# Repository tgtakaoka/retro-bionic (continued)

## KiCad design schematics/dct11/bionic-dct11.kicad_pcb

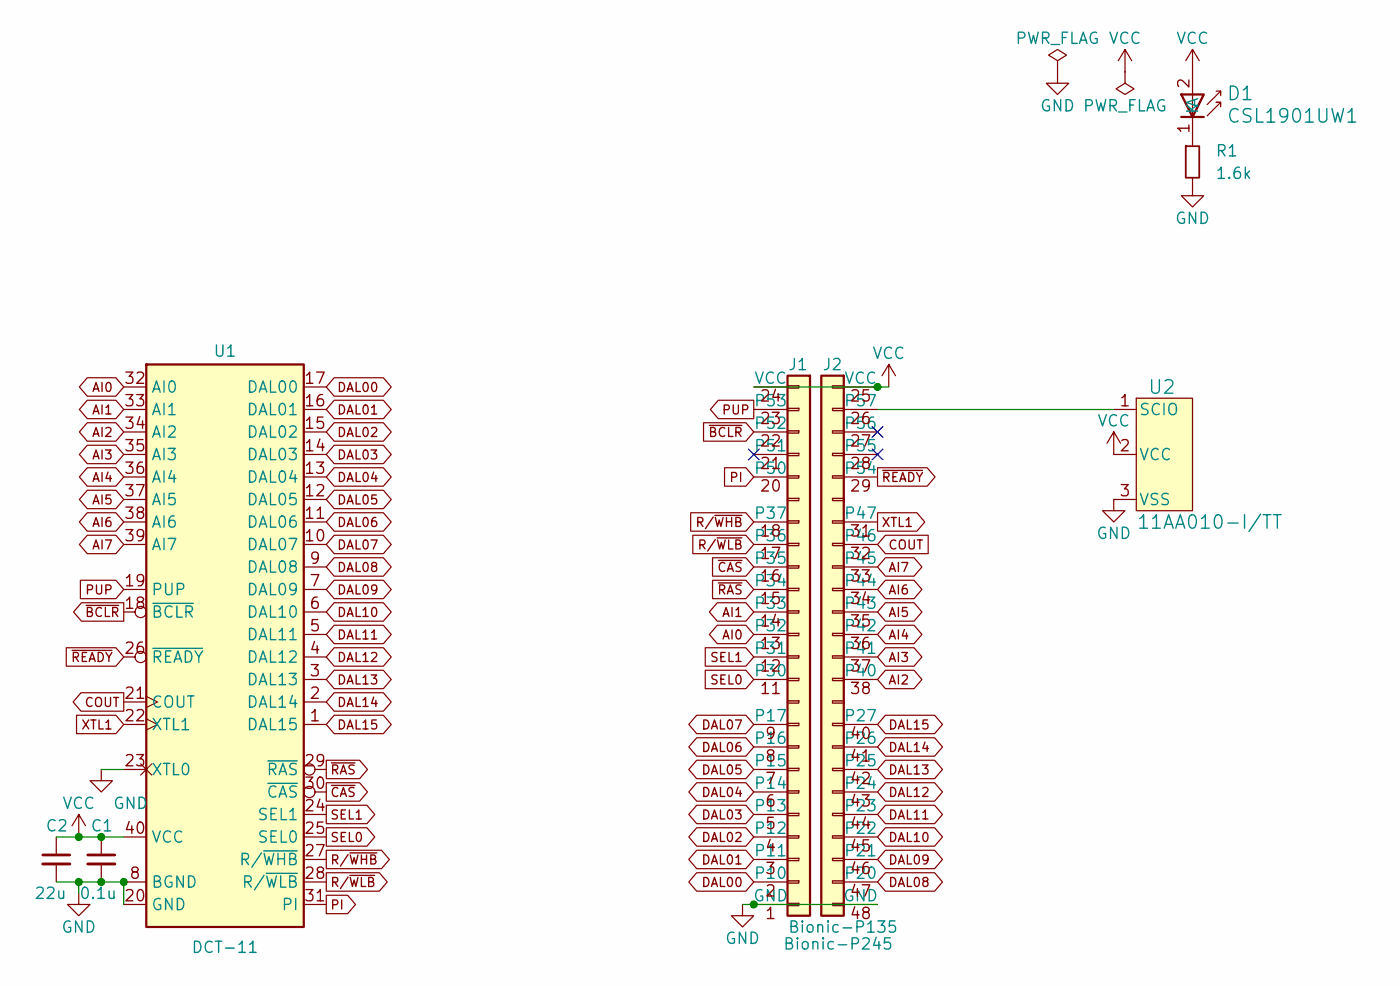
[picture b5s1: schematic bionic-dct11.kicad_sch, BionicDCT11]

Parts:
C1: 0.1u; C_0603_1608Metric_Pad1.08x0.95mm_HandSolder
C2: 22u; C_0603_1608Metric_Pad1.08x0.95mm_HandSolder
D1: CSL1901UW1; LED_CSL1901UW1_ROM-M
J1: Bionic-P135; Bionic-P135_THT
J2: Bionic-P245; Bionic-P245_THT
R1: 1.6k; R_0603_1608Metric_Pad0.98x0.95mm_HandSolder
U1: DCT-11; DIP-40_W15.24mm_Socket
U2: 11AA010-I/TT; SOT-23_MC_MCH-M

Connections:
AI0: J1.13 (P32), U1.32 (AI0)
AI1: J1.14 (P33), U1.33 (AI1)
AI2: J2.38 (P40), U1.34 (AI2)
AI3: J2.37 (P41), U1.35 (AI3)
AI4: J2.36 (P42), U1.36 (AI4)
AI5: J2.35 (P43), U1.37 (AI5)
AI6: J2.34 (P44), U1.38 (AI6)
AI7: J2.33 (P45), U1.39 (AI7)
COUT: J2.32 (P46), U1.21 (COUT)
DAL00: J1.2 (P10), U1.17 (DAL00)
DAL01: J1.3 (P11), U1.16 (DAL01)
DAL02: J1.4 (P12), U1.15 (DAL02)
DAL03: J1.5 (P13), U1.14 (DAL03)
DAL04: J1.6 (P14), U1.13 (DAL04)
DAL05: J1.7 (P15), U1.12 (DAL05)
DAL06: J1.8 (P16), U1.11 (DAL06)
DAL07: J1.9 (P17), U1.10 (DAL07)
DAL08: J2.47 (P20), U1.9 (DAL08)
DAL09: J2.46 (P21), U1.7 (DAL09)
DAL10: J2.45 (P22), U1.6 (DAL10)
DAL11: J2.44 (P23), U1.5 (DAL11)
DAL12: J2.43 (P24), U1.4 (DAL12)
DAL13: J2.42 (P25), U1.3 (DAL13)
DAL14: J2.41 (P26), U1.2 (DAL14)
DAL15: J2.40 (P27), U1.1 (DAL15)
GND: C1.2, C2.2, J1.1 (GND), J2.48 (GND), R1.2, U1.8 (BGND), U1.20 (GND), U1.23 (XTL0), U2.3 (VSS)
unnamed: D1.1 (K), R1.1
unnamed: J2.26 (P57), U2.1 (SCIO)
PI: J1.20 (P50), U1.31 (PI)
PUP: J1.23 (P53), U1.19 (PUP)
R/~WHB: J1.18 (P37), U1.27 (R/~WHB)
R/~WLB: J1.17 (P36), U1.28 (R/~WLB)
SEL0: J1.11 (P30), U1.25 (SEL0)
SEL1: J1.12 (P31), U1.24 (SEL1)
VCC: C1.1, C2.1, D1.2 (A), J1.24 (VCC), J2.25 (VCC), U1.40 (VCC), U2.2 (VCC)
XTL1: J2.31 (P47), U1.22 (XTL1)
~BCLR: J1.22 (P52), U1.18 (~BCLR)
~CAS: J1.16 (P35), U1.30 (~CAS)
~RAS: J1.15 (P34), U1.29 (~RAS)
~READY: J2.29 (P54), U1.26 (~READY)

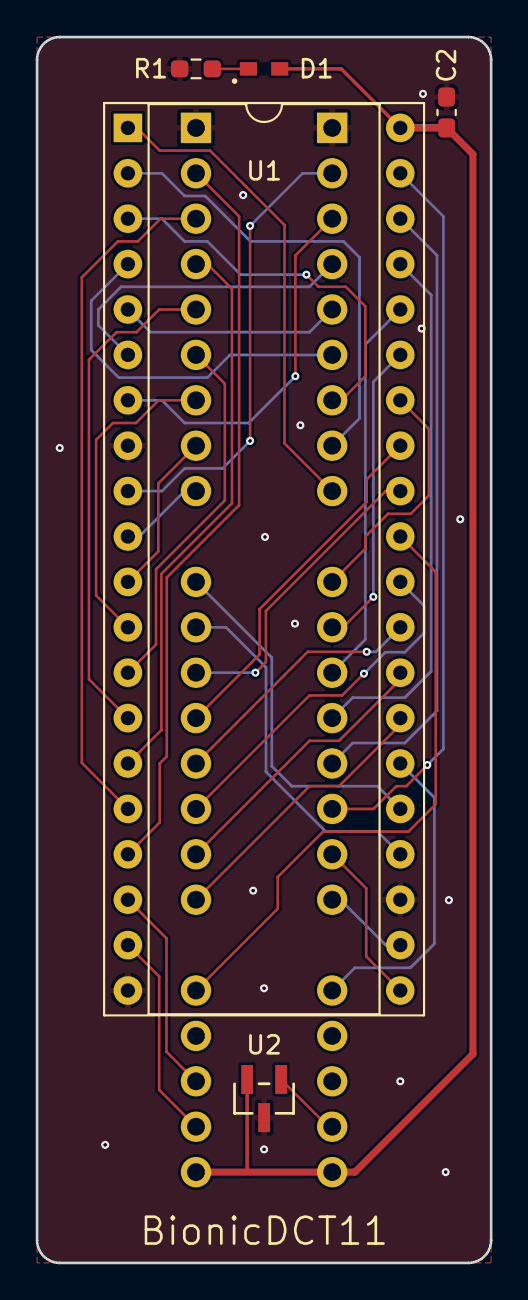
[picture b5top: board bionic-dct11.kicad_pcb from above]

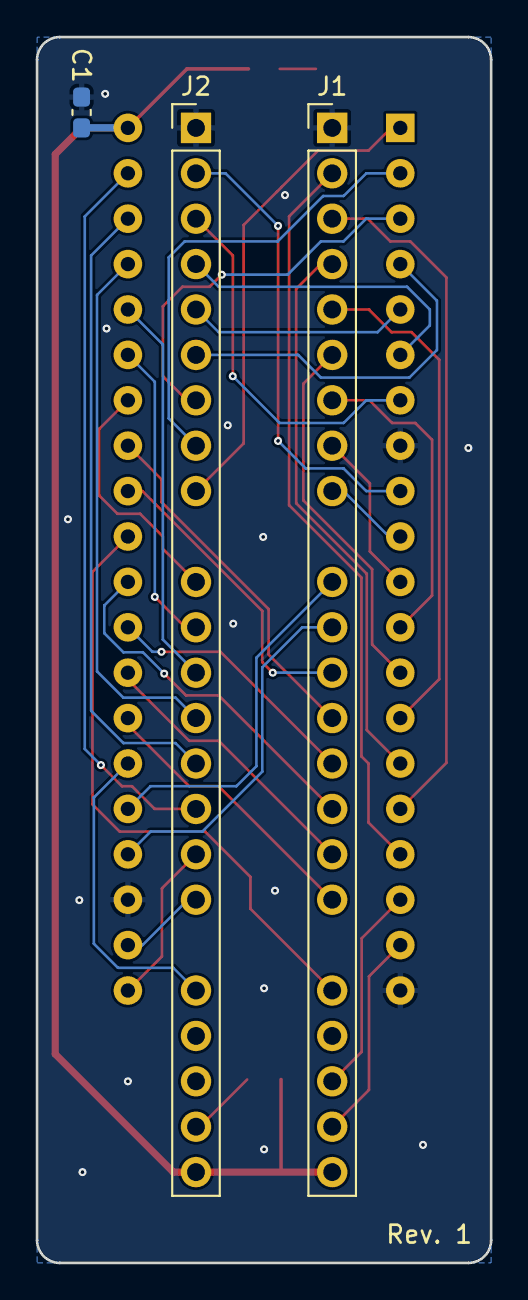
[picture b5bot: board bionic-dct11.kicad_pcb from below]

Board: 2 copper layers, 25.4 x 68.6 mm, 8 parts (3 on the bottom side), 40 nets.

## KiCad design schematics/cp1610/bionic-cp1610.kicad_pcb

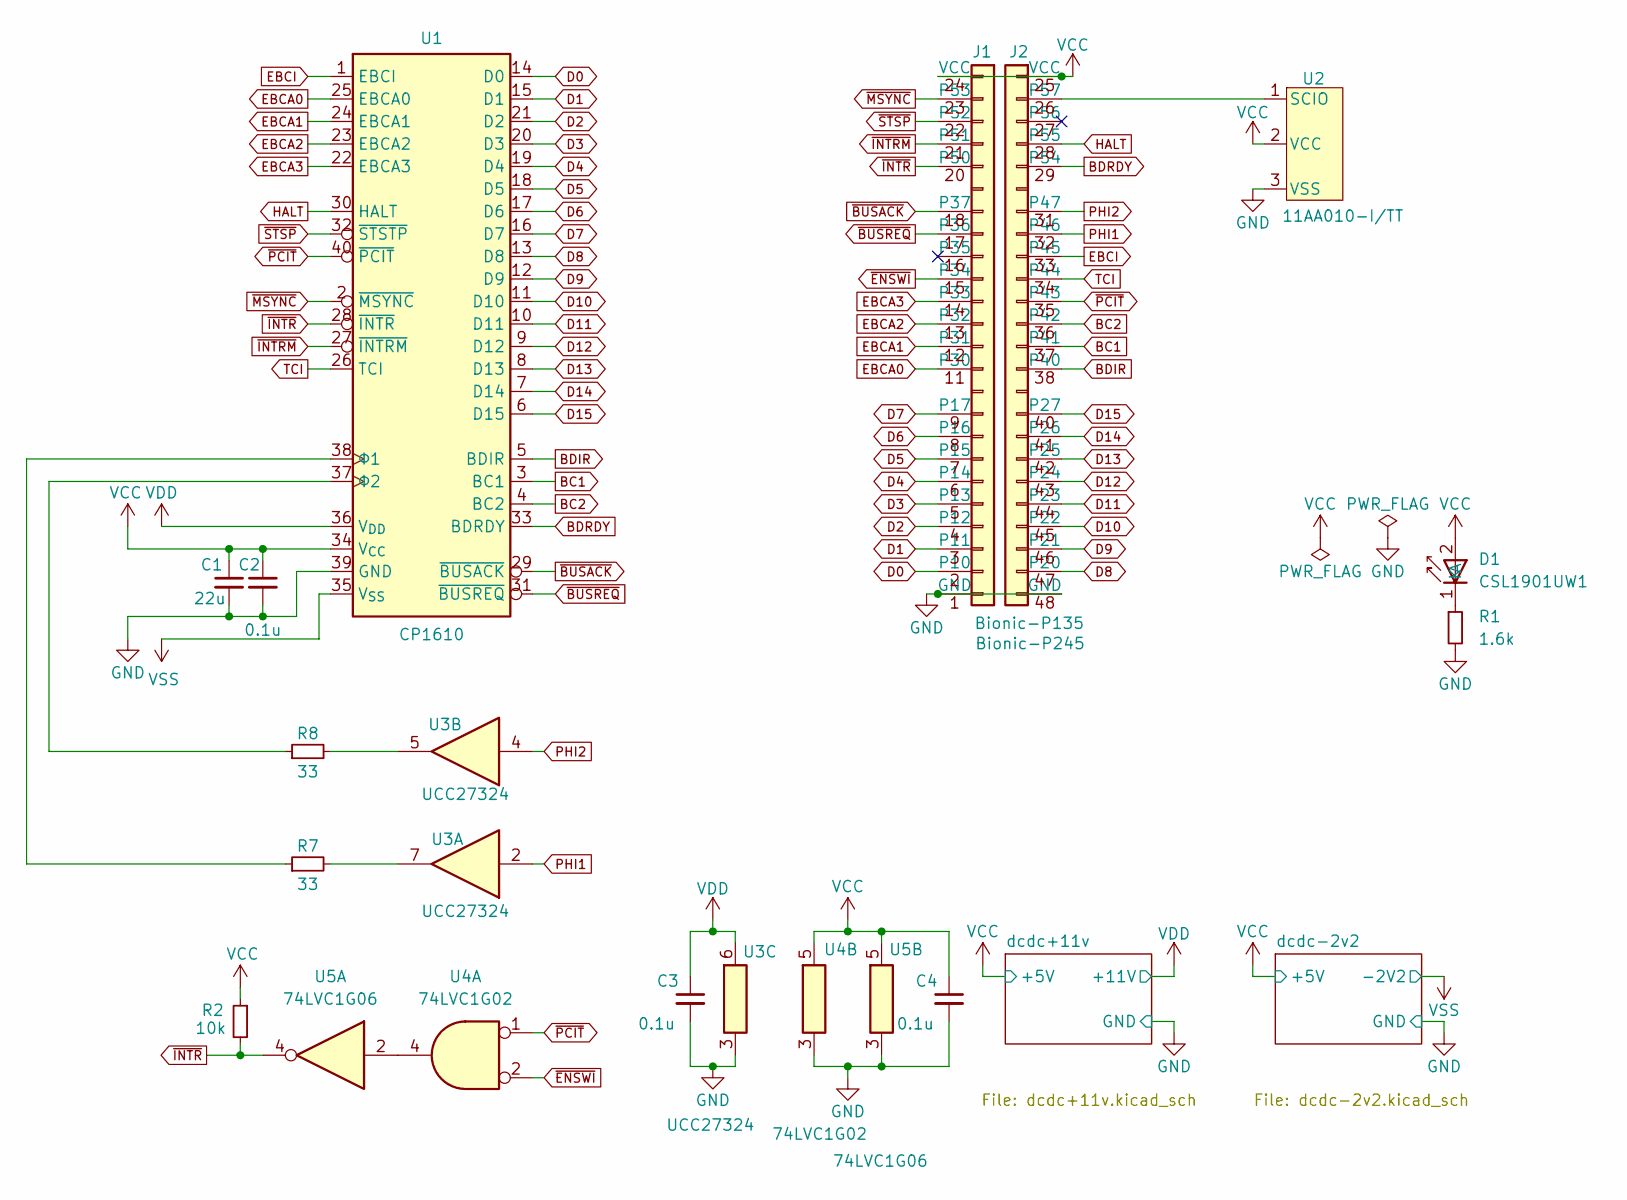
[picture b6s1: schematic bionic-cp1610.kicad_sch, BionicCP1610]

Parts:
C1: 22u; C_0603_1608Metric_Pad1.08x0.95mm_HandSolder
C2, C3, C4: 0.1u; C_0603_1608Metric_Pad1.08x0.95mm_HandSolder
D1: CSL1901UW1; LED_CSL1901UW1_ROM-M
J1: Bionic-P135; Bionic-P135_SMT
J2: Bionic-P245; Bionic-P245_SMT
R1: 1.6k; R_0603_1608Metric_Pad0.98x0.95mm_HandSolder
R2: 10k; R_0603_1608Metric_Pad0.98x0.95mm_HandSolder
R7, R8: 33; R_0603_1608Metric
U1: CP1610; DIP-40_W15.24mm_Socket
U2: 11AA010-I/TT; SOT-23_MC_MCH-M
U3: UCC27324; DGN8-M
U4: 74LVC1G02; DBV5-M
U5: 74LVC1G06; DBV5-M

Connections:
BC1: J2.37 (P41), U1.3 (BC1)
BC2: J2.36 (P42), U1.4 (BC2)
BDIR: J2.38 (P40), U1.5 (BDIR)
BDRDY: J2.29 (P54), U1.33 (BDRDY)
D0: J1.2 (P10), U1.14 (D0)
D1: J1.3 (P11), U1.15 (D1)
D2: J1.4 (P12), U1.21 (D2)
D3: J1.5 (P13), U1.20 (D3)
D4: J1.6 (P14), U1.19 (D4)
D5: J1.7 (P15), U1.18 (D5)
D6: J1.8 (P16), U1.17 (D6)
D7: J1.9 (P17), U1.16 (D7)
D8: J2.47 (P20), U1.13 (D8)
D9: J2.46 (P21), U1.12 (D9)
D10: J2.45 (P22), U1.11 (D10)
D11: J2.44 (P23), U1.10 (D11)
D12: J2.43 (P24), U1.9 (D12)
D13: J2.42 (P25), U1.8 (D13)
D14: J2.41 (P26), U1.7 (D14)
D15: J2.40 (P27), U1.6 (D15)
EBCA0: J1.11 (P30), U1.25 (EBCA0)
EBCA1: J1.12 (P31), U1.24 (EBCA1)
EBCA2: J1.13 (P32), U1.23 (EBCA2)
EBCA3: J1.14 (P33), U1.22 (EBCA3)
EBCI: J2.33 (P45), U1.1 (EBCI)
GND: C1.2, C2.2, C3.2, C4.2, J1.1 (GND), J2.48 (GND), R1.2, U1.39 (GND), U2.3 (VSS), U3.3 (GND), U4.3 (GND), U5.3 (GND); also elsewhere on the board
HALT: J2.28 (P55), U1.30 (HALT)
unnamed: D1.1 (K), R1.1
unnamed: J2.26 (P57), U2.1 (SCIO)
unnamed: R7.1, U1.38 (Φ1)
unnamed: R8.1, U1.37 (Φ2)
unnamed: R7.2, U3.7 (OUTA)
unnamed: R8.2, U3.5 (OUTB)
unnamed: U4.4, U5.2
PHI1: J2.32 (P46), U3.2 (INA)
PHI2: J2.31 (P47), U3.4 (INB)
TCI: J2.34 (P44), U1.26 (TCI)
VCC: C1.1, C2.1, C4.1, D1.2 (A), J1.24 (VCC), J2.25 (VCC), R2.1, U1.34 (V_{CC}), U2.2 (VCC), U4.5 (VCC), U5.5 (VCC); also elsewhere on the board
VDD: C3.1, U1.36 (V_{DD}), U3.6 (VDD); also elsewhere on the board
VSS: U1.35 (V_{SS}); also elsewhere on the board
~BUSACK: J1.18 (P37), U1.29 (~BUSACK)
~BUSREQ: J1.17 (P36), U1.31 (~BUSREQ)
~ENSWI: J1.15 (P34), U4.2
~INTRM: J1.21 (P51), U1.27 (~INTRM)
~INTR: J1.20 (P50), R2.2, U1.28 (~INTR), U5.4
~MSYNC: J1.23 (P53), U1.2 (~MSYNC)
~PCIT: J2.35 (P43), U1.40 (~PCIT), U4.1
~STSP: J1.22 (P52), U1.32 (~STSTP)

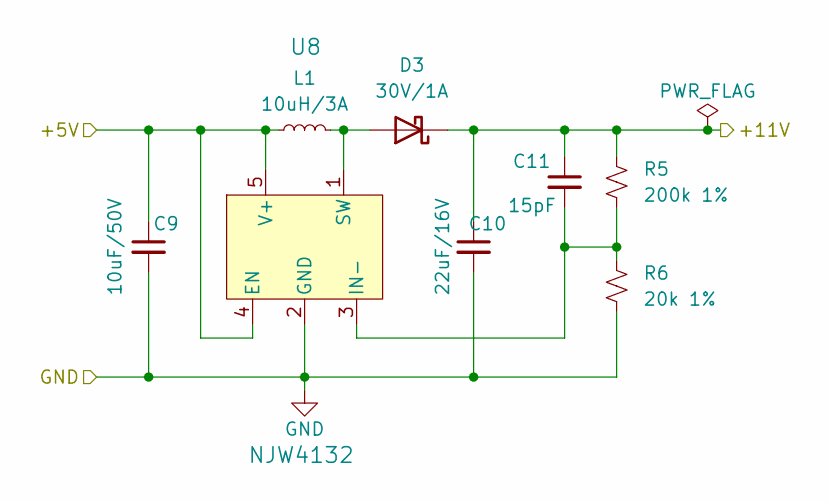
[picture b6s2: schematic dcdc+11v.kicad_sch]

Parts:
C9: 10uF/50V; C_0603_1608Metric_Pad1.08x0.95mm_HandSolder
C10: 22uF/16V; C_0603_1608Metric_Pad1.08x0.95mm_HandSolder
C11: 15pF; C_0603_1608Metric_Pad1.08x0.95mm_HandSolder
D3: 30V/1A; CR_60M-60_ROM-M
L1: 10uH/3A; IND_DFE322512F_MUR-M
R5: 200k 1%; R_0603_1608Metric_Pad0.98x0.95mm_HandSolder
R6: 20k 1%; R_0603_1608Metric_Pad0.98x0.95mm_HandSolder
U8: NJW4132; SOT-89-5_NMD-M

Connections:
GND: C9.2, C10.2, R6.2, U8.2 (GND); also elsewhere on the board
unnamed: D3.2 (A), L1.2, U8.1 (SW)
unnamed: C11.2, R5.2, R6.1, U8.3 (IN-)
VCC: C9.1, L1.1, U8.4 (EN), U8.5 (V+); also elsewhere on the board
VDD: C10.1, C11.1, D3.1 (K), R5.1; also elsewhere on the board

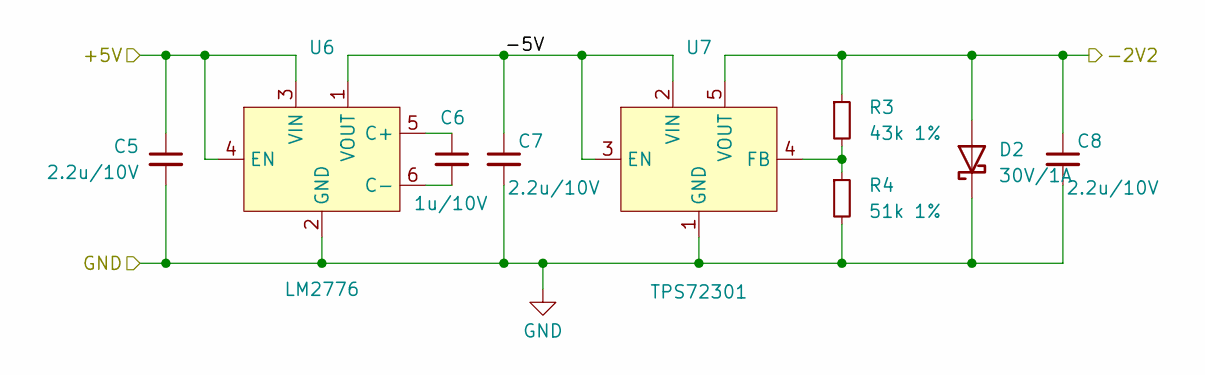
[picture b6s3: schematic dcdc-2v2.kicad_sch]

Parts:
C5, C7, C8: 2.2u/10V; C_0603_1608Metric_Pad1.08x0.95mm_HandSolder
C6: 1u/10V; C_0603_1608Metric_Pad1.08x0.95mm_HandSolder
D2: 30V/1A; CR_60M-60_ROM-M
R3: 43k 1%; R_0603_1608Metric_Pad0.98x0.95mm_HandSolder
R4: 51k 1%; R_0603_1608Metric_Pad0.98x0.95mm_HandSolder
U6: LM2776; DBV0006A_M
U7: TPS72301; DBV5-M

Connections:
/dcdc-2v2/-5V: C7.1, U6.1 (VOUT), U7.2 (VIN), U7.3 (EN)
GND: C5.2, C7.2, C8.2, D2.1 (K), R4.2, U6.2 (GND), U7.1 (GND); also elsewhere on the board
unnamed: C6.1, U6.5 (C+)
unnamed: C6.2, U6.6 (C-)
unnamed: R3.2, R4.1, U7.4 (FB)
VCC: C5.1, U6.3 (VIN), U6.4 (EN); also elsewhere on the board
VSS: C8.1, D2.2 (A), R3.1, U7.5 (VOUT); also elsewhere on the board

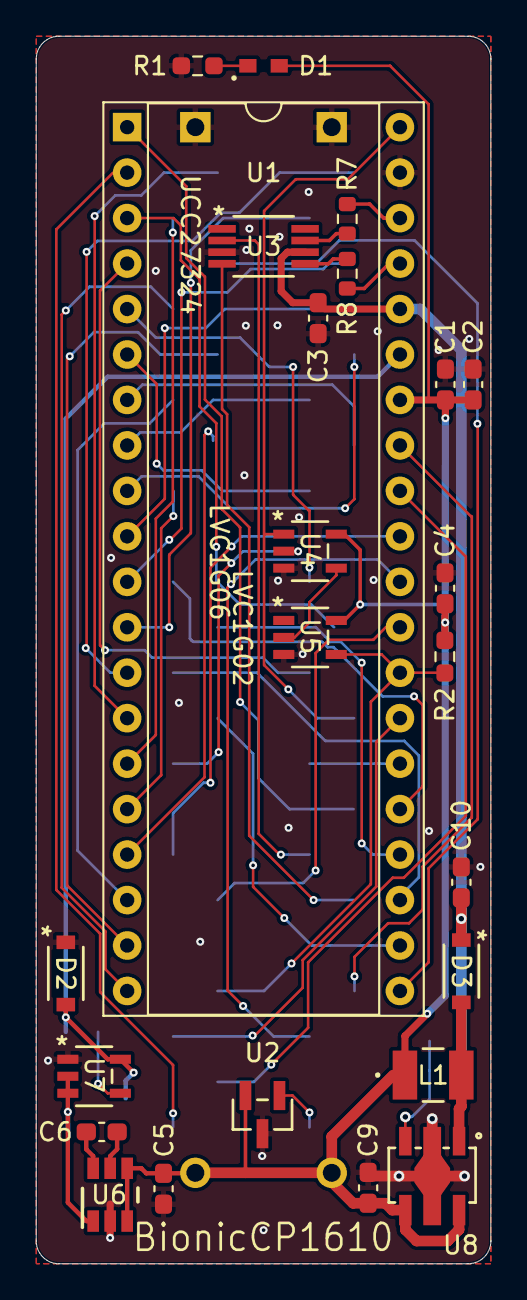
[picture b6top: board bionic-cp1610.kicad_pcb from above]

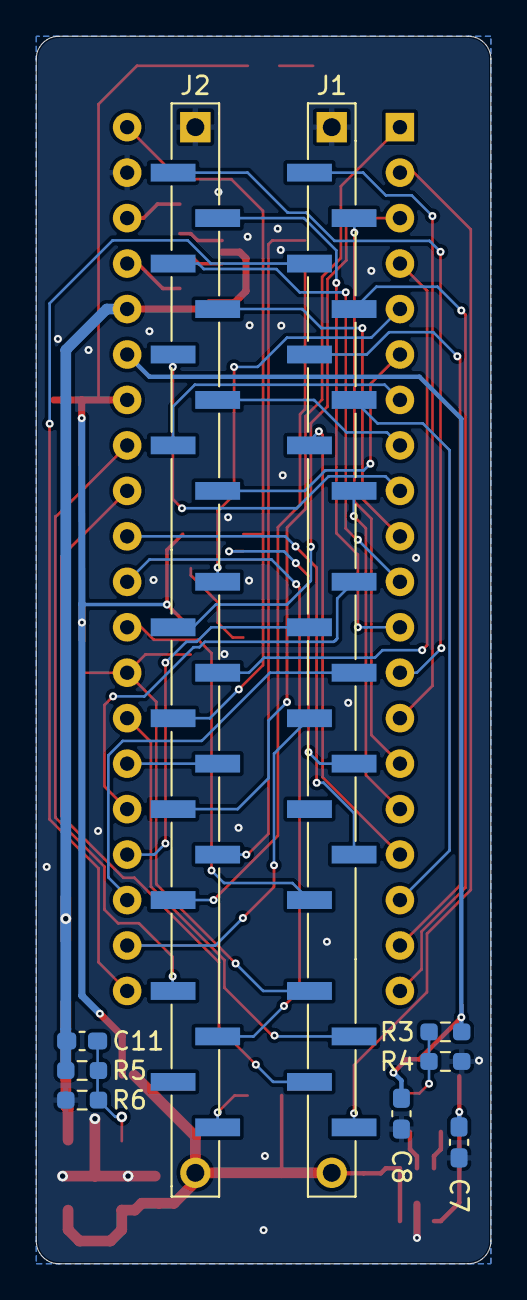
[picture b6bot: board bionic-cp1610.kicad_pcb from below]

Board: 2 copper layers, 25.4 x 68.6 mm, 33 parts (9 on the bottom side), 54 nets.

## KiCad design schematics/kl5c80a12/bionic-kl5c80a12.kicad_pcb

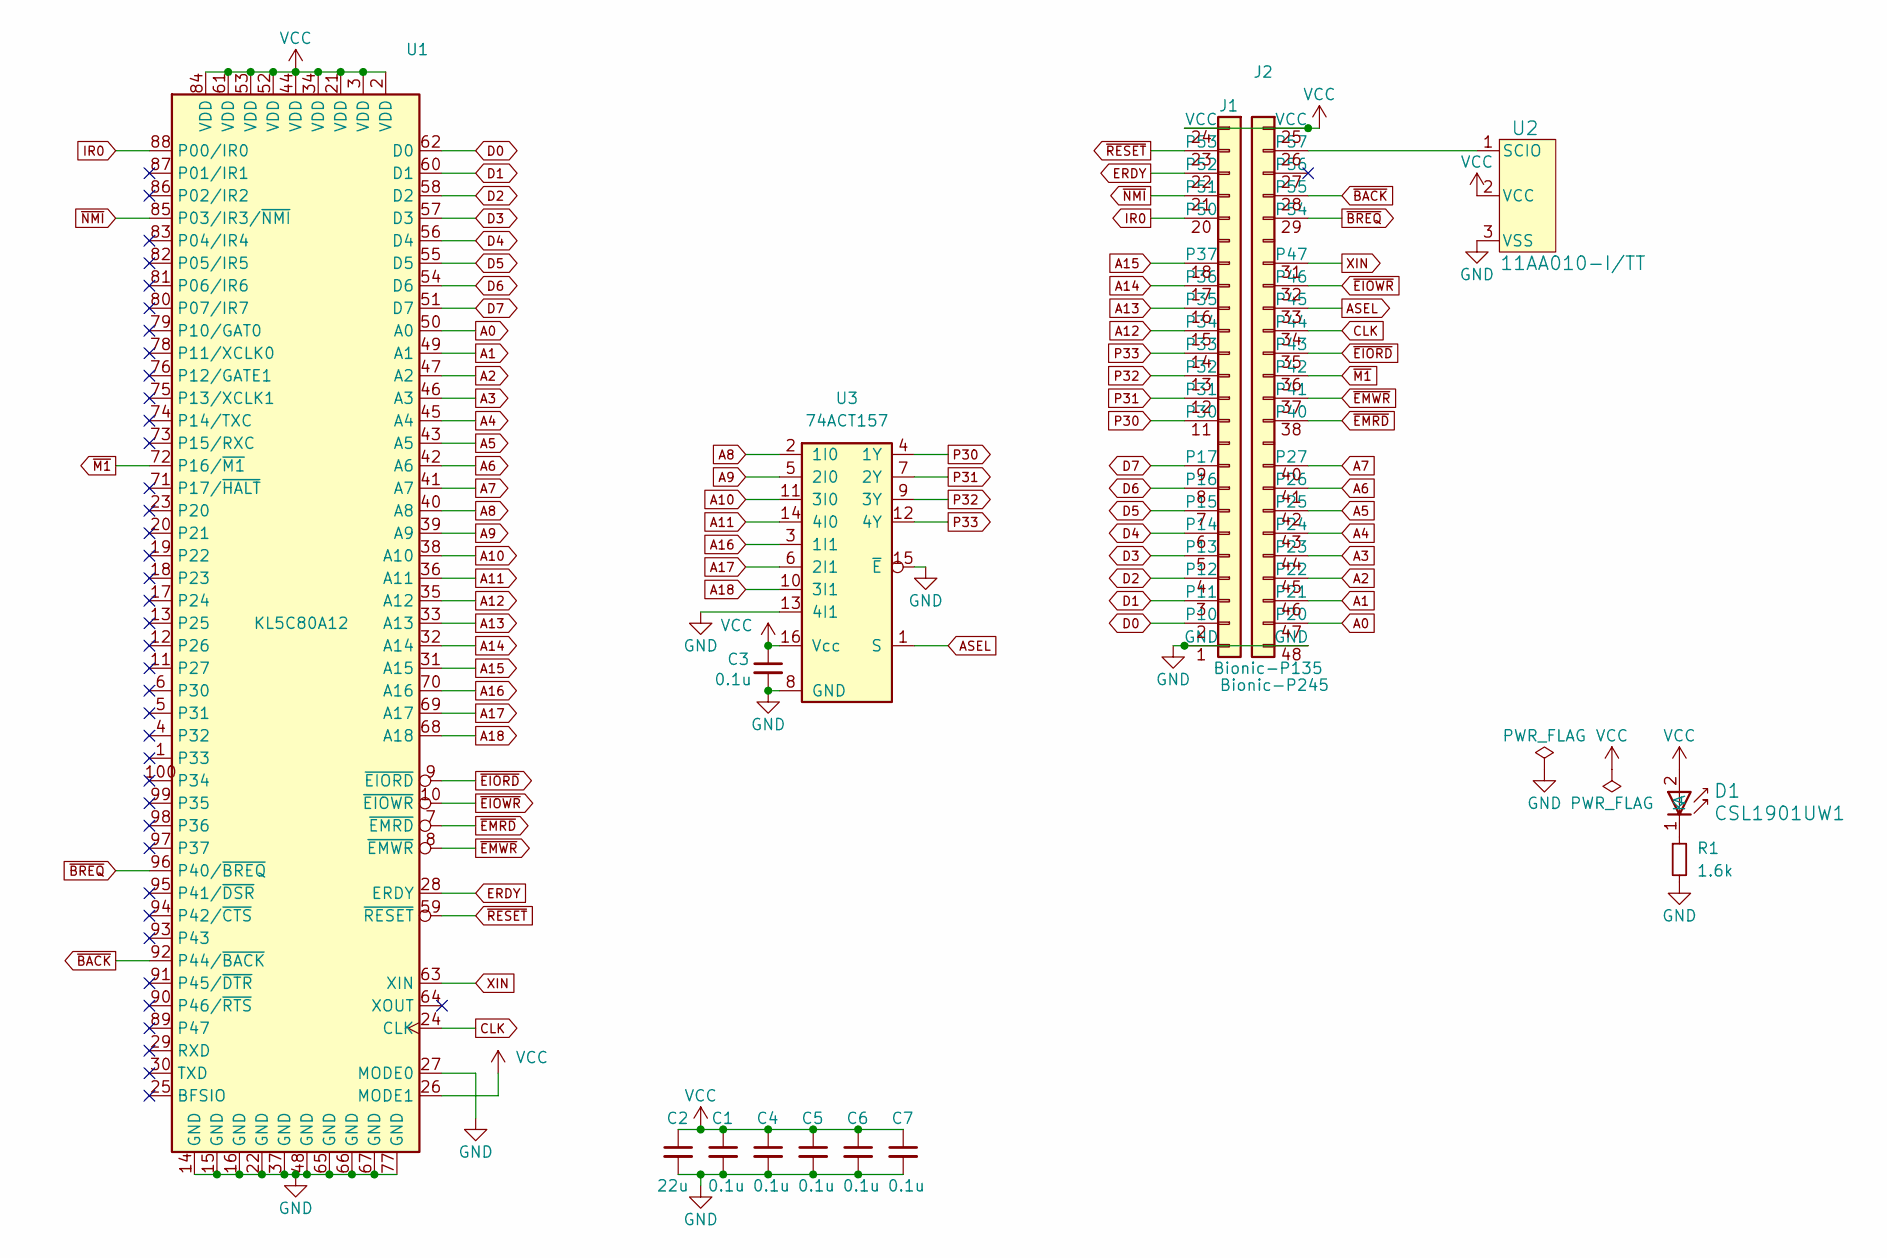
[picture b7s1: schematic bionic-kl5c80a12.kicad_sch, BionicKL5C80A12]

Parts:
C1, C3, C4, C5, C6, C7: 0.1u; C_0603_1608Metric_Pad1.08x0.95mm_HandSolder
C2: 22u; C_0603_1608Metric_Pad1.08x0.95mm_HandSolder
D1: CSL1901UW1; LED_CSL1901UW1_ROM-M
J1: Bionic-P135; Bionic-P135_SMT
J2: Bionic-P245; Bionic-P245_SMT
R1: 1.6k; R_0603_1608Metric_Pad0.98x0.95mm_HandSolder
U1: KL5C80A12; PQFP-100_14x20mm_P0.65mm
U2: 11AA010-I/TT; SOT-23_MC_MCH-M
U3: 74ACT157; PW16-M

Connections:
A0: J2.47 (P20), U1.50 (A0)
A1: J2.46 (P21), U1.49 (A1)
A2: J2.45 (P22), U1.47 (A2)
A3: J2.44 (P23), U1.46 (A3)
A4: J2.43 (P24), U1.45 (A4)
A5: J2.42 (P25), U1.43 (A5)
A6: J2.41 (P26), U1.42 (A6)
A7: J2.40 (P27), U1.41 (A7)
A8: U1.40 (A8), U3.2 (1I0)
A9: U1.39 (A9), U3.5 (2I0)
A10: U1.38 (A10), U3.11 (3I0)
A11: U1.36 (A11), U3.14 (4I0)
A12: J1.15 (P34), U1.35 (A12)
A13: J1.16 (P35), U1.33 (A13)
A14: J1.17 (P36), U1.32 (A14)
A15: J1.18 (P37), U1.31 (A15)
A16: U1.70 (A16), U3.3 (1I1)
A17: U1.69 (A17), U3.6 (2I1)
A18: U1.68 (A18), U3.10 (3I1)
ASEL: J2.33 (P45), U3.1 (S)
CLK: J2.34 (P44), U1.24 (CLK)
D0: J1.2 (P10), U1.62 (D0)
D1: J1.3 (P11), U1.60 (D1)
D2: J1.4 (P12), U1.58 (D2)
D3: J1.5 (P13), U1.57 (D3)
D4: J1.6 (P14), U1.56 (D4)
D5: J1.7 (P15), U1.55 (D5)
D6: J1.8 (P16), U1.54 (D6)
D7: J1.9 (P17), U1.51 (D7)
ERDY: J1.22 (P52), U1.28 (ERDY)
GND: C1.2, C2.2, C3.2, C4.2, C5.2, C6.2, C7.2, J1.1 (GND), J2.48 (GND), R1.2, U1.14 (GND), U1.15 (GND), U1.16 (GND), U1.22 (GND), U1.27 (MODE0), U1.37 (GND), U1.48 (GND), U1.65 (GND), U1.66 (GND), U1.67 (GND), U1.77 (GND), U2.3 (VSS), U3.8 (GND), U3.13 (4I1), U3.15 (~E)
IR0: J1.20 (P50), U1.88 (P00/IR0)
unnamed: D1.1 (K), R1.1
unnamed: J2.26 (P57), U2.1 (SCIO)
P30: J1.11 (P30), U3.4 (1Y)
P31: J1.12 (P31), U3.7 (2Y)
P32: J1.13 (P32), U3.9 (3Y)
P33: J1.14 (P33), U3.12 (4Y)
VCC: C1.1, C2.1, C3.1, C4.1, C5.1, C6.1, C7.1, D1.2 (A), J1.24 (VCC), J2.25 (VCC), U1.2 (VDD), U1.3 (VDD), U1.21 (VDD), U1.26 (MODE1), U1.34 (VDD), U1.44 (VDD), U1.52 (VDD), U1.53 (VDD), U1.61 (VDD), U1.84 (VDD), U2.2 (VCC), U3.16 (Vcc)
XIN: J2.31 (P47), U1.63 (XIN)
~BACK: J2.28 (P55), U1.92 (P44/~BACK)
~BREQ: J2.29 (P54), U1.96 (P40/~BREQ)
~EIORD: J2.35 (P43), U1.9 (~EIORD)
~EIOWR: J2.32 (P46), U1.10 (~EIOWR)
~EMRD: J2.38 (P40), U1.7 (~EMRD)
~EMWR: J2.37 (P41), U1.8 (~EMWR)
~M1: J2.36 (P42), U1.72 (P16/~M1)
~NMI: J1.21 (P51), U1.85 (P03/IR3/~NMI)
~RESET: J1.23 (P53), U1.59 (~RESET)

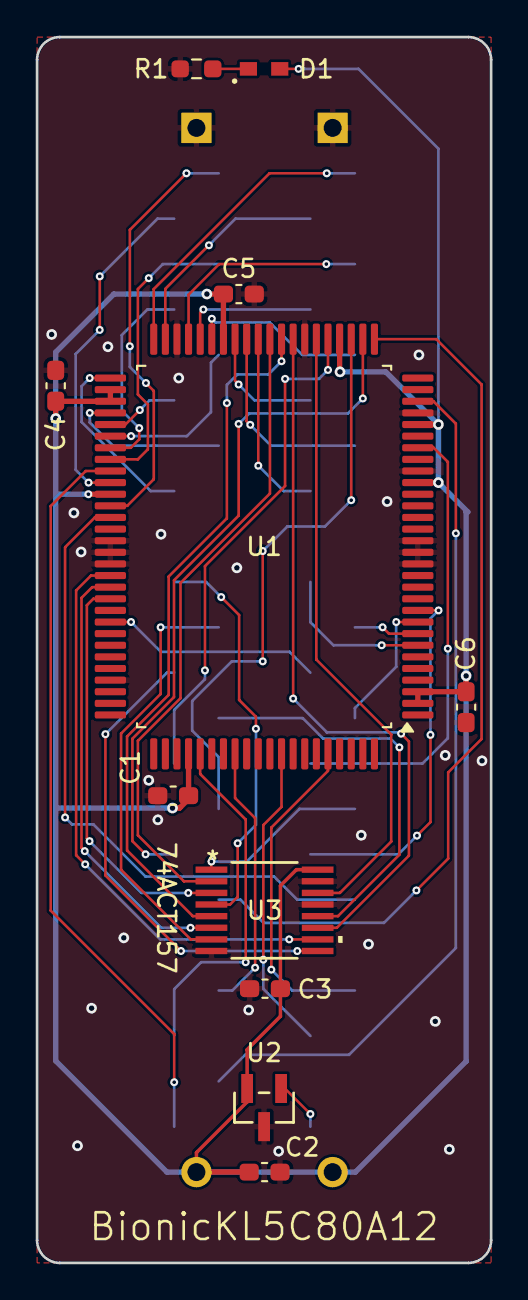
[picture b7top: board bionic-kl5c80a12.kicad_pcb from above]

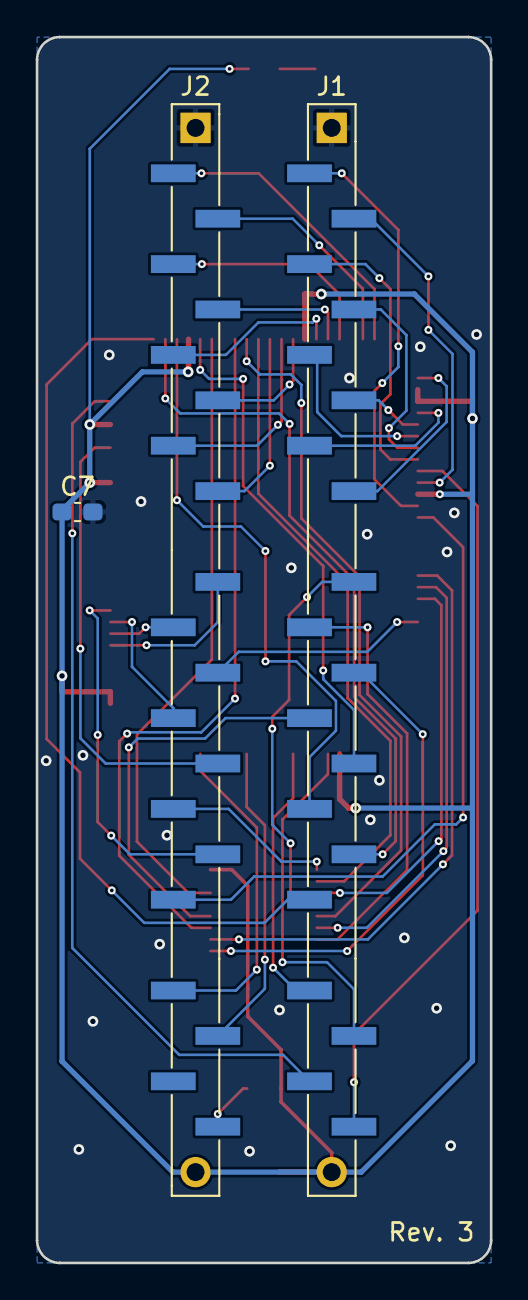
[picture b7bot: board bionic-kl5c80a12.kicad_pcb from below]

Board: 2 copper layers, 25.4 x 68.6 mm, 14 parts (3 on the bottom side), 49 nets.

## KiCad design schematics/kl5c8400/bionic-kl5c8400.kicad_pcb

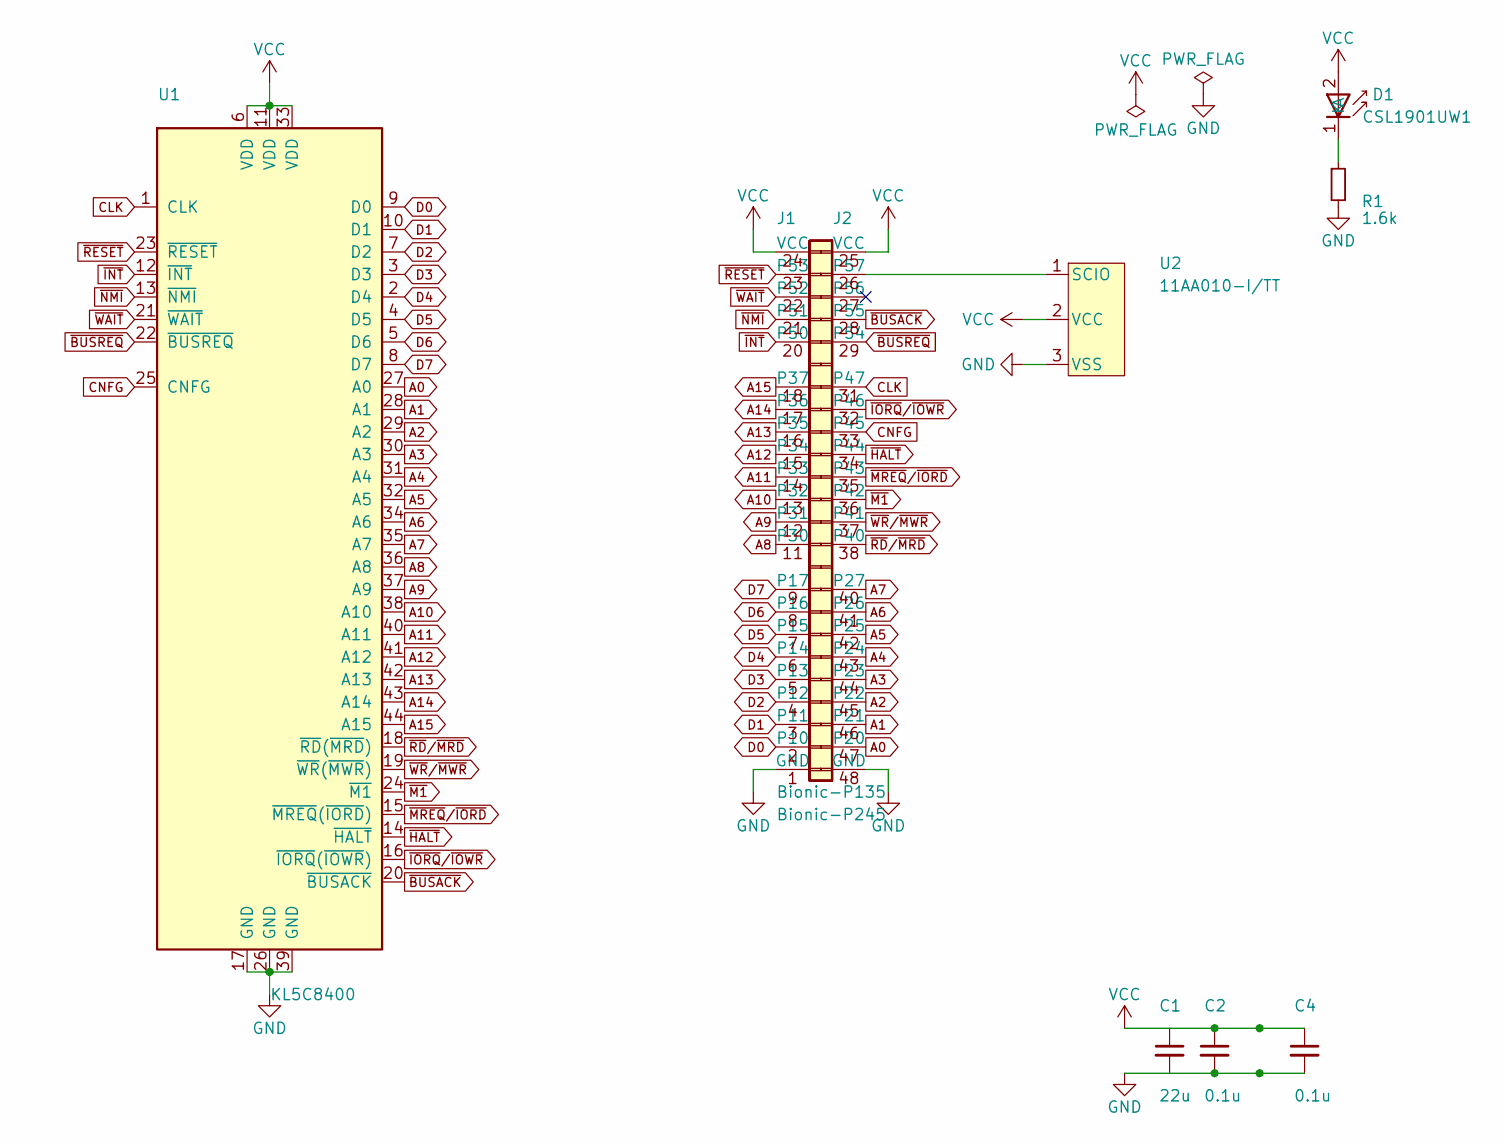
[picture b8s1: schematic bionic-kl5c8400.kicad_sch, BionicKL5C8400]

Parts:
C1: 22u; C_0603_1608Metric_Pad1.08x0.95mm_HandSolder
C2, C4: 0.1u; C_0603_1608Metric_Pad1.08x0.95mm_HandSolder
D1: CSL1901UW1; LED_CSL1901UW1_ROM-M
J1: Bionic-P135; Bionic-P135_SMT
J2: Bionic-P245; Bionic-P245_SMT
R1: 1.6k; R_0603_1608Metric_Pad0.98x0.95mm_HandSolder
U1: KL5C8400; QFP-44_10x10mm_P0.8mm_Kawasaki
U2: 11AA010-I/TT; SOT-23_MC_MCH-M

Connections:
A0: J2.47 (P20), U1.27 (A0)
A1: J2.46 (P21), U1.28 (A1)
A2: J2.45 (P22), U1.29 (A2)
A3: J2.44 (P23), U1.30 (A3)
A4: J2.43 (P24), U1.31 (A4)
A5: J2.42 (P25), U1.32 (A5)
A6: J2.41 (P26), U1.34 (A6)
A7: J2.40 (P27), U1.35 (A7)
A8: J1.11 (P30), U1.36 (A8)
A9: J1.12 (P31), U1.37 (A9)
A10: J1.13 (P32), U1.38 (A10)
A11: J1.14 (P33), U1.40 (A11)
A12: J1.15 (P34), U1.41 (A12)
A13: J1.16 (P35), U1.42 (A13)
A14: J1.17 (P36), U1.43 (A14)
A15: J1.18 (P37), U1.44 (A15)
CLK: J2.31 (P47), U1.1 (CLK)
CNFG: J2.33 (P45), U1.25 (CNFG)
D0: J1.2 (P10), U1.9 (D0)
D1: J1.3 (P11), U1.10 (D1)
D2: J1.4 (P12), U1.7 (D2)
D3: J1.5 (P13), U1.3 (D3)
D4: J1.6 (P14), U1.2 (D4)
D5: J1.7 (P15), U1.4 (D5)
D6: J1.8 (P16), U1.5 (D6)
D7: J1.9 (P17), U1.8 (D7)
GND: C1.2, C2.2, C4.2, J1.1 (GND), J2.48 (GND), R1.2, U1.17 (GND), U1.26 (GND), U1.39 (GND), U2.3 (VSS)
unnamed: D1.1 (K), R1.1
unnamed: J2.26 (P57), U2.1 (SCIO)
VCC: C1.1, C2.1, C4.1, D1.2 (A), J1.24 (VCC), J2.25 (VCC), U1.6 (VDD), U1.11 (VDD), U1.33 (VDD), U2.2 (VCC)
~BUSACK: J2.28 (P55), U1.20 (~BUSACK)
~BUSREQ: J2.29 (P54), U1.22 (~BUSREQ)
~HALT: J2.34 (P44), U1.14 (~HALT)
~INT: J1.20 (P50), U1.12 (~INT)
~IORQ/~IOWR: J2.32 (P46), U1.16 (~IORQ(~IOWR))
~M1: J2.36 (P42), U1.24 (~M1)
~MREQ/~IORD: J2.35 (P43), U1.15 (~MREQ(~IORD))
~NMI: J1.21 (P51), U1.13 (~NMI)
~RD/~MRD: J2.38 (P40), U1.18 (~RD(~MRD))
~RESET: J1.23 (P53), U1.23 (~RESET)
~WAIT: J1.22 (P52), U1.21 (~WAIT)
~WR/~MWR: J2.37 (P41), U1.19 (~WR(~MWR))

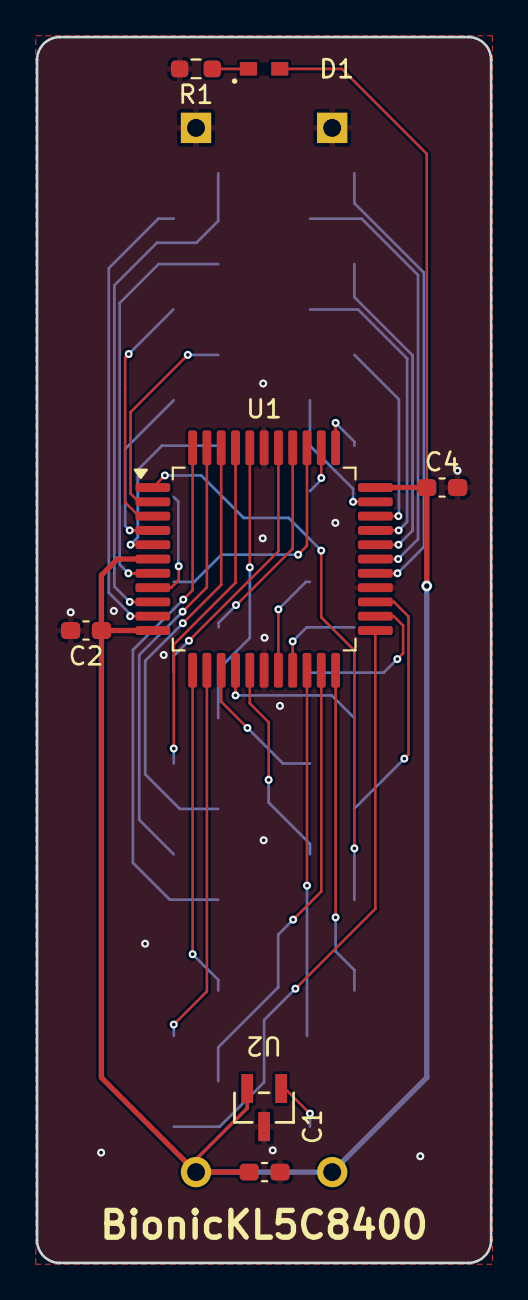
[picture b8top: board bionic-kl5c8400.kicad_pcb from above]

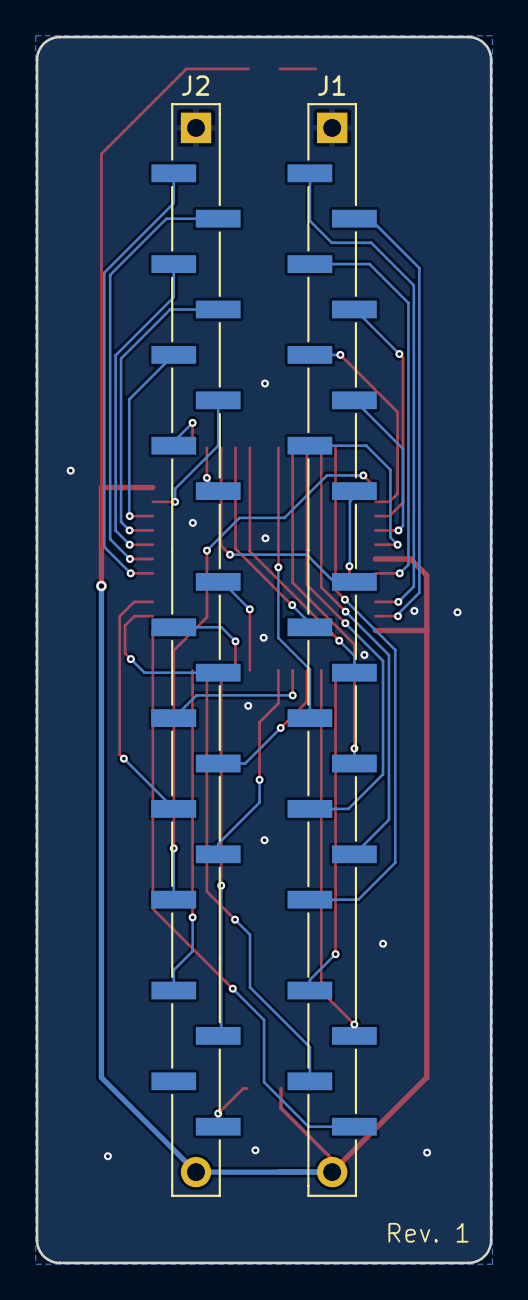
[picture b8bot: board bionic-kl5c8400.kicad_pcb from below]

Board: 2 copper layers, 25.4 x 68.6 mm, 9 parts (2 on the bottom side), 42 nets.
